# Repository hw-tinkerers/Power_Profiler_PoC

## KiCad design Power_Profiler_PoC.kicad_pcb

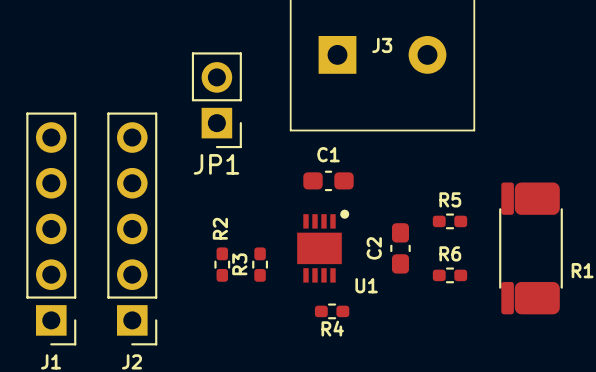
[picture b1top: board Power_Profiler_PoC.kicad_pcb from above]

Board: 2 copper layers, 13 parts (0 on the bottom side), 11 nets.

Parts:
C1: 1uF; C_0603_1608Metric_Pad1.08x0.95mm_HandSolder
C2: 100nF; C_0603_1608Metric_Pad1.08x0.95mm_HandSolder
J1: Conn_01x05_Pin; PinHeader_1x05_P2.54mm_Vertical
J2: Conn_01x05_Socket; PinHeader_1x05_P2.54mm_Vertical
J3: Screw_Terminal_01x02; 2P_Screw_Terminal
JP1: Jumper_2_Open; PinHeader_1x02_P2.54mm_Vertical
R1: 5mE; R_2512_6332Metric
R2, R3, R4: 2k; R_0402_1005Metric_Pad0.72x0.64mm_HandSolder
R5, R6: 100E; R_0402_1005Metric_Pad0.72x0.64mm_HandSolder
U1: LTC2944IDD#PBF; LTC2944_DFN

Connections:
/3V3/5V: J1.4, J2.4, JP1.1 (A), R2.1, R3.1, R4.1
/Ext_Connector/BATT+_IN: J3.1, JP1.2 (B)
/Ext_Connector/BATT+_OUT: J3.2, R1.4
/LTC2944/SENSE+_IN: C1.2, C2.2, R5.1, U1.1 (SENSE+)
/LTC2944/SENSE-_IN: C2.1, R6.1, U1.8 (SENSE-)
/SCL: J1.1, J2.1, R2.2, U1.4 (SCL)
/SDA: J1.2, J2.2, R3.2, U1.5 (SDA)
/~ALCC: J1.3, J2.3, R4.2, U1.6 (~ALCC)
GND: C1.1, J1.5, J2.5, R1.1, U1.2 (GND_1), U1.3 (GND_2), U1.7 (GND_3), U1.9 (EP)
unnamed: R1.2, R6.2
unnamed: R1.3, R5.2

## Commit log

2024-03-18 Schematics started
2024-03-22 Assigned footprints
2024-03-24 Started routing
